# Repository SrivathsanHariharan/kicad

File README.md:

# kicad
this is for checking github

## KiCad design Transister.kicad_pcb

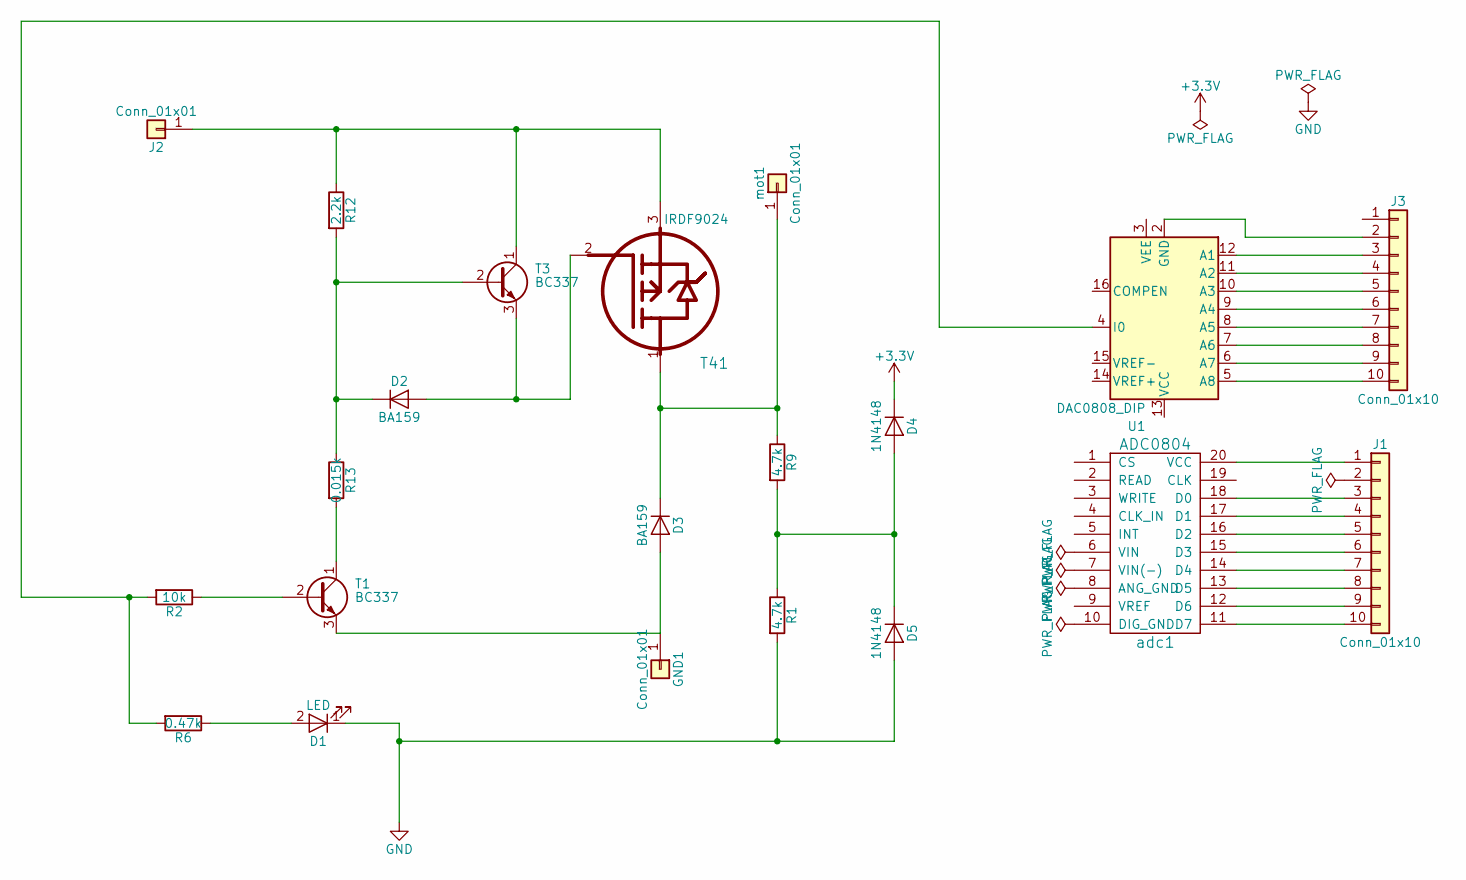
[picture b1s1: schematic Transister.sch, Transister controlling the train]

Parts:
D1: LED; DCDC-Conv_CINCON_EC5BEXX_Dual
D2, D3: BA159; D_DO-41_SOD81_P10.16mm_Horizontal
D4, D5: 1N4148; D_DO-35_SOD27_P7.62mm_Horizontal
GND1: Conn_01x01; 1pin
J1, J3: Conn_01x10; Pin_Header_Straight_1x10_Pitch1.27mm
J2: Conn_01x01; 1pin
R1, R9: 4.7k; R_Axial_DIN0516_L15.5mm_D5.0mm_P25.40mm_Horizontal
R2: 10k; R_Axial_DIN0516_L15.5mm_D5.0mm_P25.40mm_Horizontal
R6: 0.47k; R_Axial_DIN0516_L15.5mm_D5.0mm_P25.40mm_Horizontal
R12: 2.2k; R_Axial_DIN0516_L15.5mm_D5.0mm_P25.40mm_Horizontal
R13: 0.015k; R_Axial_DIN0516_L15.5mm_D5.0mm_P25.40mm_Horizontal
T1, T3: BC337; TO-92_Molded_Narrow
T41: IRDF9024; TO-92_Molded_Narrow
U1: DAC0808_DIP; DIP-20_W7.62mm
adc1: ADC0804; DIP-20_W7.62mm
mot1: Conn_01x01; 1pin

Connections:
+3V3: D4.1 (K)
GND: D1.1 (K), D5.2 (A), R1.2
unnamed: D1.2 (A), R6.1
unnamed: D2.1 (K), R12.2, R13.1, T3.2 (B)
unnamed: D2.2 (A), T3.3 (E), T41.2
unnamed: D3.1 (K), R9.1, T41.1, mot1.1
unnamed: D3.2 (A), GND1.1, T1.3 (E)
unnamed: D4.2 (A), D5.1 (K), R1.1, R9.2
unnamed: J1.1, adc1.20 (VCC)
unnamed: J1.3, adc1.18 (D0)
unnamed: J1.4, adc1.17 (D1)
unnamed: J1.5, adc1.16 (D2)
unnamed: J1.6, adc1.15 (D3)
unnamed: J1.7, adc1.14 (D4)
unnamed: J1.8, adc1.13 (D5)
unnamed: J1.9, adc1.12 (D6)
unnamed: J1.10, adc1.11 (D7)
unnamed: J2.1, R12.1, T3.1 (C), T41.3
unnamed: J3.2, U1.2 (GND)
unnamed: J3.3, U1.12 (A1)
unnamed: J3.4, U1.11 (A2)
unnamed: J3.5, U1.10 (A3)
unnamed: J3.6, U1.9 (A4)
unnamed: J3.7, U1.8 (A5)
unnamed: J3.8, U1.7 (A6)
unnamed: J3.9, U1.6 (A7)
unnamed: J3.10, U1.5 (A8)
unnamed: R2.1, T1.2 (B)
unnamed: R2.2, R6.2, U1.4 (I0)
unnamed: R13.2, T1.1 (C)

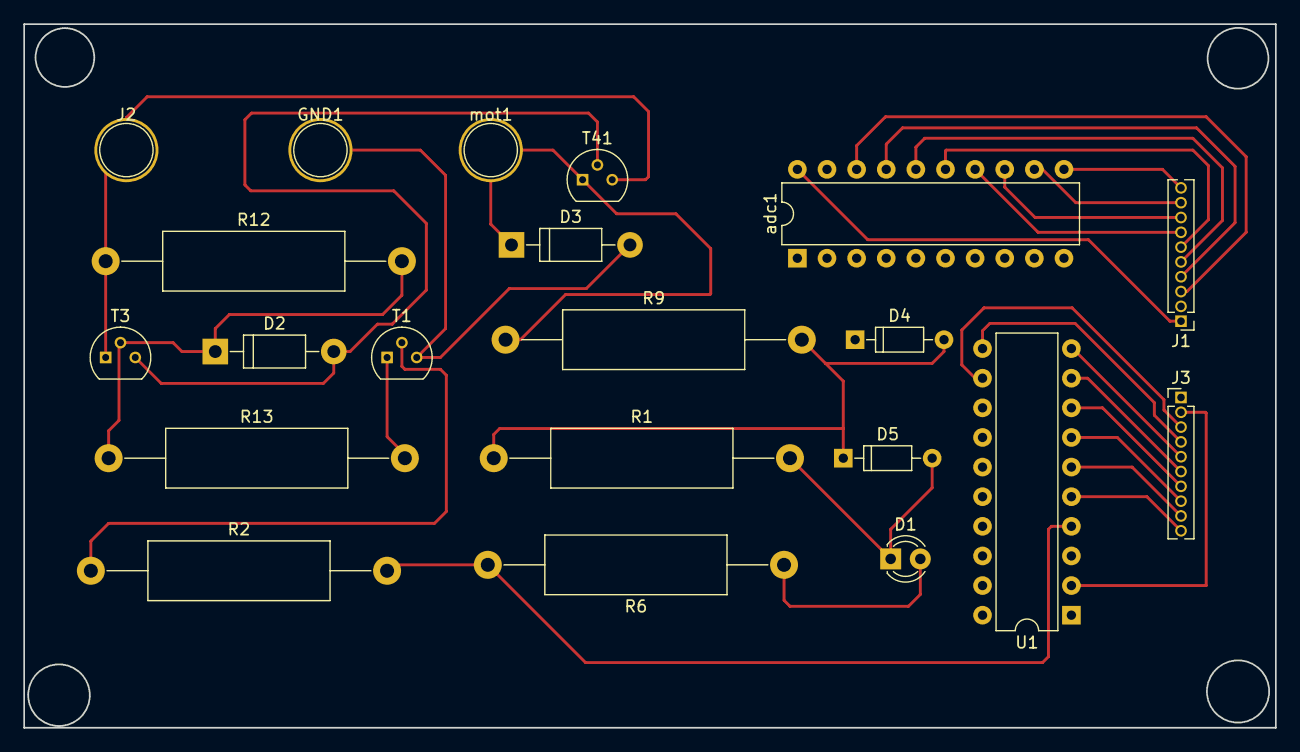
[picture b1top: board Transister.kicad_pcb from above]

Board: 2 copper layers, 107.3 x 60.3 mm, 21 parts (0 on the bottom side), 29 nets.
